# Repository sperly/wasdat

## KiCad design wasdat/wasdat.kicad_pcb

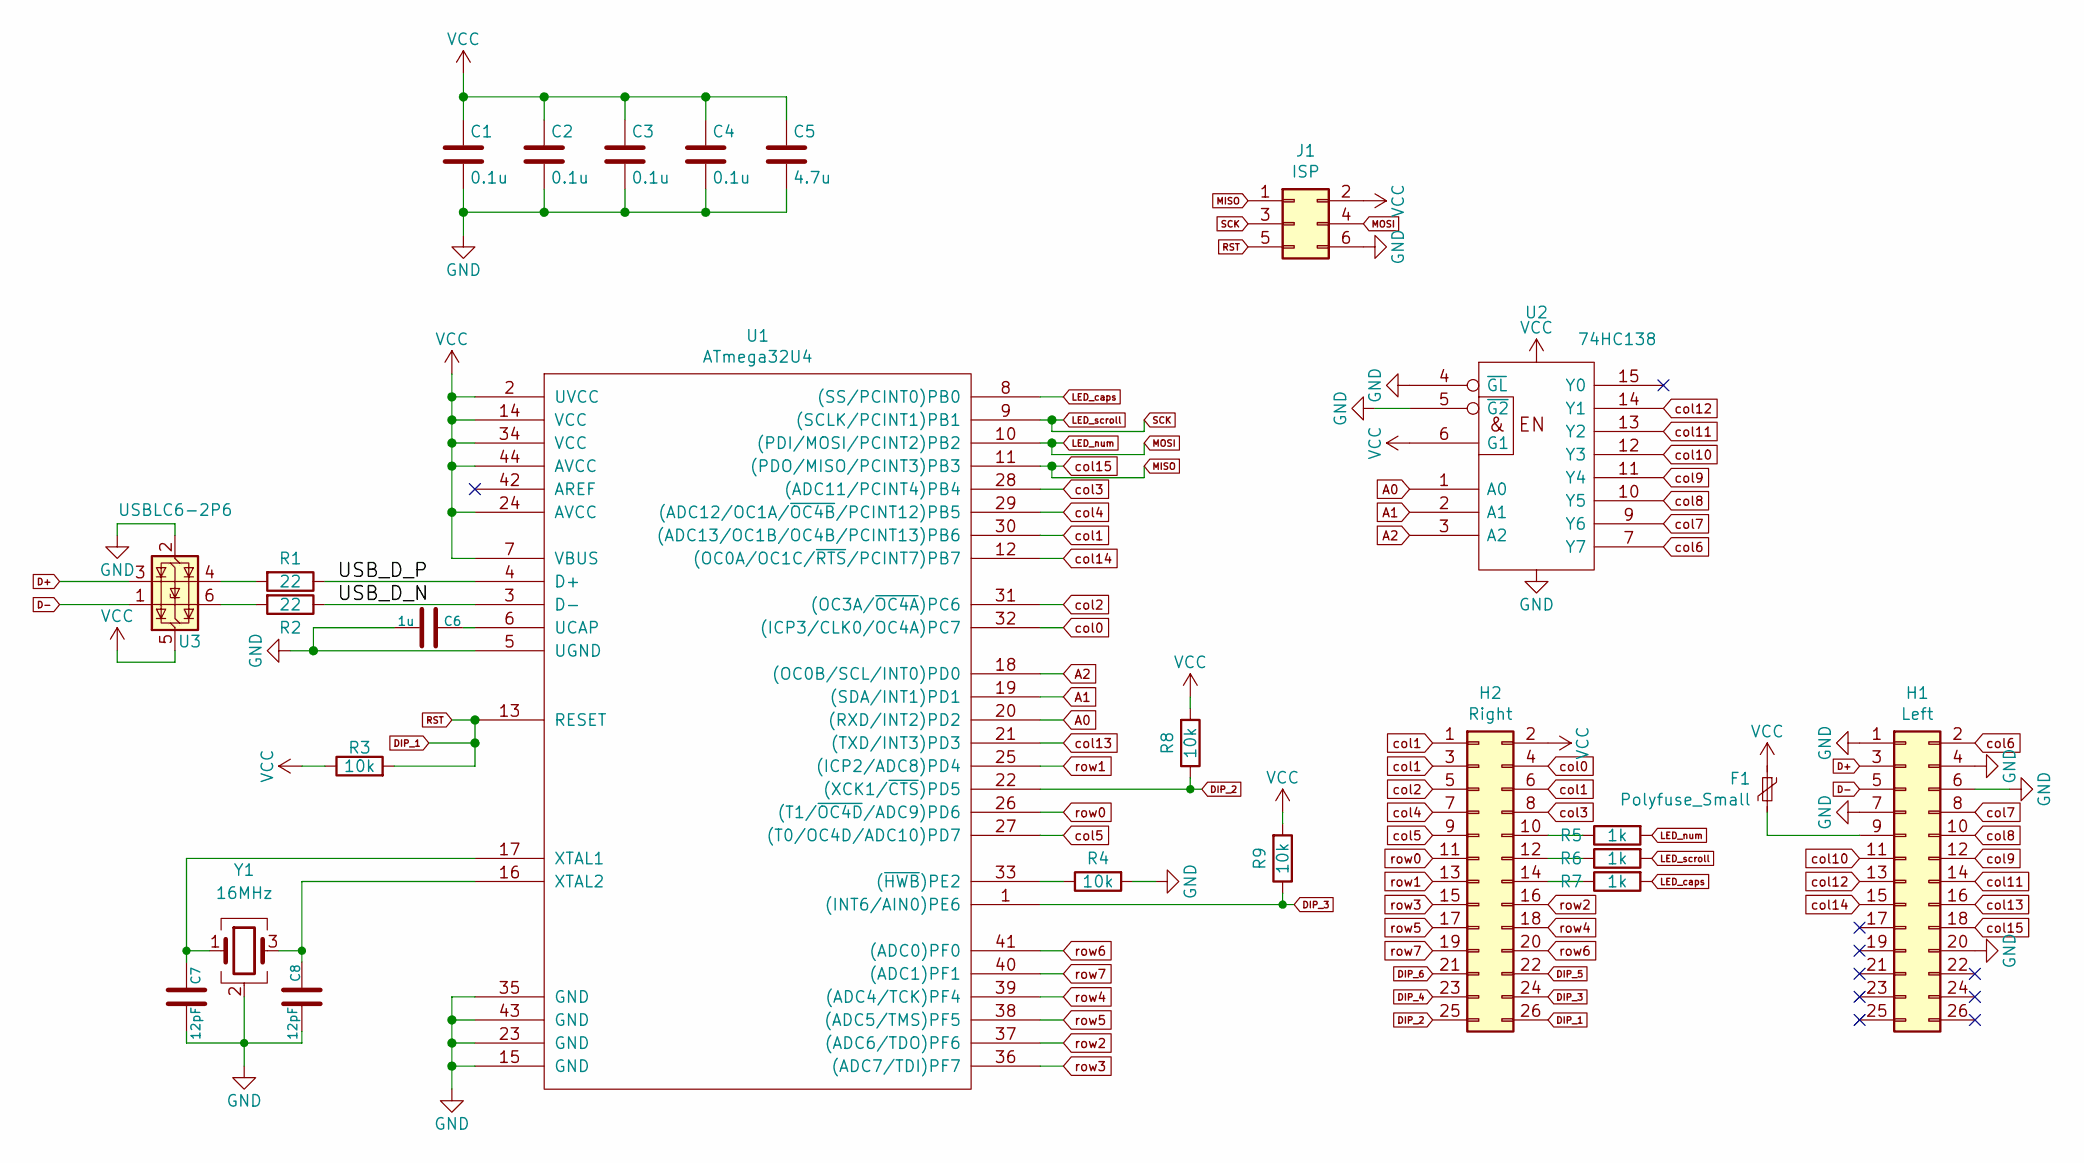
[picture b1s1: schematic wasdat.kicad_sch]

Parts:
C1, C2, C3, C4: 0.1u; C_0402_1005Metric; LCSC C1525
C5: 4.7u; C_0603_1608Metric; LCSC C19666
C6: 1u; C_0402_1005Metric; LCSC C52923
C7, C8: 12pF; C_0402_1005Metric; LCSC C1547
F1: Polyfuse_Small; R_0805; LCSC C22435710
H1: Left; PinHeader_2x13_P2.00mm_Vertical; LCSC C2883299
H2: Right; PinHeader_2x13_P2.00mm_Vertical; LCSC C2883299
J1: ISP; PinHeader_2x03_P2.54mm_Vertical
R1, R2: 22; R_0402_1005Metric; LCSC C25092
R3, R4, R8, R9: 10k; R_0402_1005Metric; LCSC C60489
R5, R6, R7: 1k; R_0402_1005Metric; LCSC C11702
U1: ATmega32U4; QFN-44-1EP_7x7mm_P0.5mm_EP5.15x5.15mm; LCSC C112161
U2: 74HC138; TSSOP-16_4.4x5mm_P0.65mm; LCSC C157527
U3: USBLC6-2P6; SOT-666; LCSC C15999
Y1: 16MHz; Crystal_SMD_2016-4Pin_2.0x1.6mm; LCSC C254260

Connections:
/USB_D_N: R2.1, U1.3 (D-)
/USB_D_P: R1.1, U1.4 (D+)
A0: U1.20 ((RXD/INT2)PD2), U2.1 (A0)
A1: U1.19 ((SDA/INT1)PD1), U2.2 (A1)
A2: U1.18 ((OC0B/SCL/INT0)PD0), U2.3 (A2)
D+: H1.3, U3.3 (I/O2)
D-: H1.5, U3.1 (I/O1)
DIP_1: H2.26, J1.5, R3.2, U1.13 (RESET)
DIP_2: H2.25, R8.1, U1.22 ((XCK1/~CTS)PD5)
DIP_3: H2.24, R9.1, U1.1 ((INT6/AIN0)PE6)
DIP_4: H2.23
DIP_5: H2.22
DIP_6: H2.21
GND: C1.2, C2.2, C3.2, C4.2, C5.2, C6.2, C7.2, C8.2, H1.1, H1.4, H1.6, H1.7, H1.20, J1.6, R4.2, U1.5 (UGND), U1.15 (GND), U1.23 (GND), U1.35 (GND), U1.43 (GND), U2.4 (~GL), U2.5 (~G2), U2.8 (GND), U3.2 (GND), Y1.2 (G), Y1.4 (G)
LED_caps: R7.2, U1.8 ((SS/PCINT0)PB0)
LED_num: J1.4, R5.2, U1.10 ((PDI/MOSI/PCINT2)PB2)
LED_scroll: J1.3, R6.2, U1.9 ((SCLK/PCINT1)PB1)
MISO: H1.18, J1.1, U1.11 ((PDO/MISO/PCINT3)PB3)
unnamed: F1.2, H1.9
unnamed: H2.10, R5.1
unnamed: H2.12, R6.1
unnamed: H2.14, R7.1
unnamed: R1.2, U3.4 (I/O2)
unnamed: R2.2, U3.6 (I/O1)
unnamed: R4.1, U1.33 ((~HWB)PE2)
unnamed: C6.1, U1.6 (UCAP)
unnamed: C7.1, U1.17 (XTAL1), Y1.1
unnamed: C8.1, U1.16 (XTAL2), Y1.3
VCC: C1.1, C2.1, C3.1, C4.1, C5.1, F1.1, H2.2, J1.2, R3.1, R8.2, R9.2, U1.2 (UVCC), U1.7 (VBUS), U1.14 (VCC), U1.24 (AVCC), U1.34 (VCC), U1.44 (AVCC), U2.6 (G1), U2.16 (VCC), U3.5 (VBUS)
col0: H2.4, U1.32 ((ICP3/CLK0/OC4A)PC7)
col1: H2.1, H2.3, H2.6, U1.30 ((ADC13/OC1B/OC4B/PCINT13)PB6)
col2: H2.5, U1.31 ((OC3A/~OC4A)PC6)
col3: H2.8, U1.28 ((ADC11/PCINT4)PB4)
col4: H2.7, U1.29 ((ADC12/OC1A/~OC4B/PCINT12)PB5)
col5: H2.9, U1.27 ((T0/OC4D/ADC10)PD7)
col6: H1.2, U2.7 (Y7)
col7: H1.8, U2.9 (Y6)
col8: H1.10, U2.10 (Y5)
col9: H1.12, U2.11 (Y4)
col10: H1.11, U2.12 (Y3)
col11: H1.14, U2.13 (Y2)
col12: H1.13, U2.14 (Y1)
col13: H1.16, U1.21 ((TXD/INT3)PD3)
col14: H1.15, U1.12 ((OC0A/OC1C/~RTS/PCINT7)PB7)
row0: H2.11, U1.26 ((T1/~OC4D/ADC9)PD6)
row1: H2.13, U1.25 ((ICP2/ADC8)PD4)
row2: H2.16, U1.37 ((ADC6/TDO)PF6)
row3: H2.15, U1.36 ((ADC7/TDI)PF7)
row4: H2.18, U1.39 ((ADC4/TCK)PF4)
row5: H2.17, U1.38 ((ADC5/TMS)PF5)
row6: H2.20, U1.41 ((ADC0)PF0)
row7: H2.19, U1.40 ((ADC1)PF1)

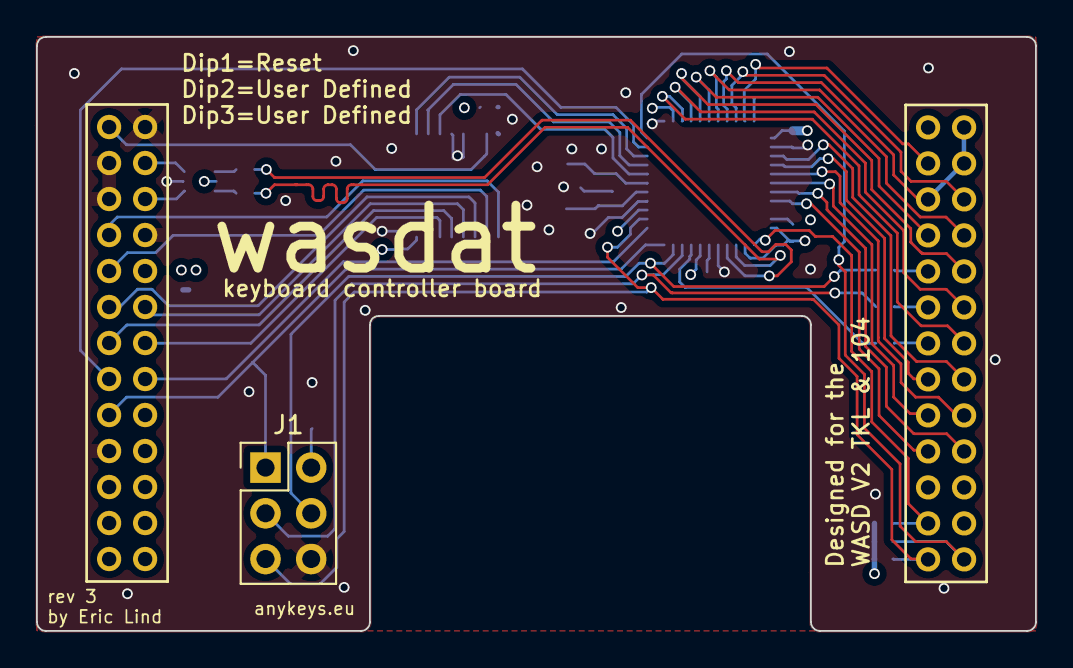
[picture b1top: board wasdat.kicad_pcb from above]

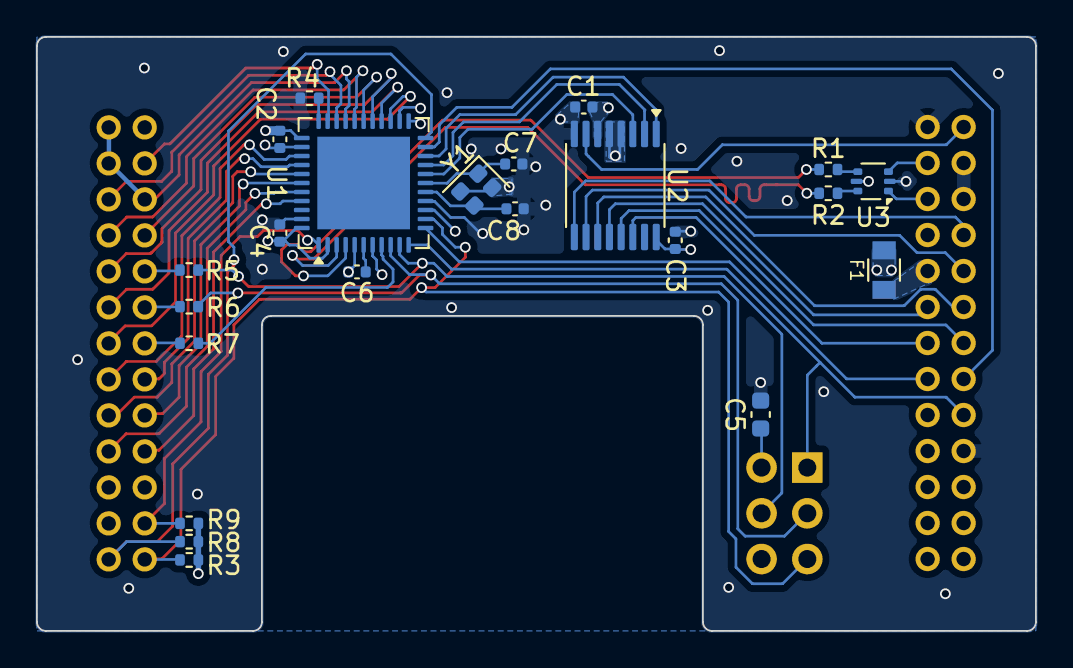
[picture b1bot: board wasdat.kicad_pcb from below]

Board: 4 copper layers, 55.5 x 33.0 mm, 25 parts (24 on the bottom side), 49 nets.

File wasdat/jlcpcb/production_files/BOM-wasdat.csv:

Comment,Designator,Footprint,LCSC,Quantity
0.1u,"C1,C2,C3,C4",C_0402_1005Metric,C1525,4
10k,"R3,R4,R8,R9",R_0402_1005Metric,C60489,4
12pF,"C7,C8",C_0402_1005Metric,C1547,2
16MHz,Y1,Crystal_SMD_2016-4Pin_2.0x1.6mm,C254260,1
1k,"R5,R6,R7",R_0402_1005Metric,C11702,3
1u,C6,C_0402_1005Metric,C52923,1
22,"R1,R2",R_0402_1005Metric,C25092,2
4.7u,C5,C_0603_1608Metric,C19666,1
74HC138,U2,TSSOP-16_4.4x5mm_P0.65mm,C157527,1
ATmega32U4,U1,QFN-44-1EP_7x7mm_P0.5mm_EP5.15x5.15mm,C112161,1
Left,H1,PinHeader_2x13_P2.00mm_Vertical,C2883299,1
Polyfuse_Small,F1,R_0805,C22435710,1
Right,H2,PinHeader_2x13_P2.00mm_Vertical,C2883299,1
USBLC6-2P6,U3,SOT-666,C15999,1
